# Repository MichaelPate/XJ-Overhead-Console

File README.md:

# XJ-Overhead-Console
Overhead Console Trip Computer for a 1990 Jeep Cherokee XJ. The goal is to display things like gyroscope readings and log GPS points.

The overhead console, or trip computer, should display the folling data by the time its fully complete:
- RTC time and date
- Temperature, pressure, humidity, both inside/outside
  - A remote mount sensor would be needed, with likely wireless radio communications
- Compass heading (cardinal and degrees)
- GPS latitude and longitude
- GPS speed (if accurate enough)
- GPS distance (calculated from sum of prior points or line-of-sight)
- Gyroscope roll and pitch
  - Gyroscope should be able to be zeroed
- Accelerometer readings that are above a threshold
  - Threshold should be settable
- System voltage
- The computer should know if the car is running or not
- The hardware circuit should provide a couple spare analog and digital IO for future use

The trip computer should be able to control the folling
- Off road lights (through relays)
  - User control of lights acheived through toggle switches
  - The ability to control off road lights gives the ability to alarm
- The horn (through a relay)
  - User control of horn acheived through pull cord mounted on side of head console
  - The ability to control the horn gives the ability to alarm
- A GSM module capable of sending SMS messages
  - This allows for GPS location in the event of a theft
  - Or possibly sending SOS messages to contacts in the event of an emergency
  - Or possibly remote kill switch capability

The trip computer should have the ability to connect to an SD card or USB flash drive:
- This allows for datalogging of all sensor data for later viewing
- Control of datalogging would be minimal. Auto generated file names.
  - User control of datalogging would be through a push button or toggle switch

A possible feature would be alarming. The alarm state could be acheived
through significant detection of motion, a GPS reading outside a geo-fence, or a combination
The addition of a PIR sensor inside the cab is possible, if experimentation shows it to not be too sensetive to activity outside the car.

# Overhead Console Project #

**1 Project Scope**

The scope of the project is to design a computer controller for a car that can provide security functionality, environmental data, locationing/positioning, and basic data logger functionality.

**1.1 Security Functionality**

The controller can provide security through the means of a fuel pump interlock system. Such a system involves interrupting power to the fuel pump when a security state is active, and returning signal to the fuel pump when the security state is inactive.

Additional security measures that may be implemented in the future are alarming (controlling lights and horn), the ability to send SMS text messages containing GPS location data, and PIR/glass-break sensors to be mounted inside the cabin. Security events may be recorded to the SD card.

**1.2 Environmental Data**

Environmental data that the computer is responsible for gathering, logging, and displaying includes temperature, atmospheric pressure, both inside and outside the cabin. A real time clock is also present that will track the time of all events and provide a readout. A low outside temperature should lead to an indication for the risk of ice on roadways.

**1.3 Locationing/Positioning Data**

The computer is also responsible for tracking location/position data. This includes GPS coordinates, gyroscope readings for pitch and roll, accelerometer readings, and compass heading. If the GPS is deemed accurate enough, GPS indicated speed and altitude should also be reported.

**1.4 Datalogging Functionality**

All normal operation data should be, optionally, recorded to an SD card by way of an SD card reader/writer. The controller will keep track of empty space on the SD card and auto-generate file names, but will not have the ability to browse or change existing files. The user will control data logging through a toggle switch.

**2 Project Requirements**

The project will have requirements for user interface, sensors, hardware, power supply, external communications (antennae, ports).

**2.1 User Interface**

The user interface will consist of a 20x4 character LCD, push buttons, toggle switches, LEDs, and a piezo buzzer. There should be 3 push buttons for menu navigation and special functions. There should be one toggle switch for security functionality and one toggle switch for controlling data-logging functions. There should be 3 LEDs for displaying the following conditions: GPS lock, SD card error, and general error. There will also be hardware reset and power switches available, though hidden from normal use.

**2.2 Sensors and Hardware, Controller**

The controller used for this project is the STM32F401RE. Discrete IO, I2C, SPI, and UART buses will be used to communicate with all modules and hardware. Time will be tracked by an RTC module that is built into the controller and powered via external coin cell battery

The I2C bus will connect the controller to the BMP280 barometric pressure sensor, the GY273 magnetometer, the GY521 accelerometer, the SHT31 humidity sensor, and the 20x4 character LCD (HD44780 with PCF8574 I2C expander). The SPI bus will be used to connect the controller to the SD card module for data logging. This is currently the only device that will utilize the SPI bus. Two UARTS will be used, one for a connection to a PC via serial terminal, and the other will be used to connect the controller to the NEO-6M GPS module. The discrete analog and digital IO will be used to interface with the LEDs, piezo, push buttons, toggle switches, and an analog system battery voltage input (through a resistive voltage divider).

All hardware should be installed on a printed circuit board (PCB) of 2 or 4 layers. All UI elements should connect to the main circuit board through JST connectors. Power should be supplied via screw terminals. If a remote sensor is installed, data and power connections should be made using screw terminals. The PCB should be smaller than approximately 4.5” by 4.5.”

**2.3 Power Supply**

The controller will require 12VDC from the car’s electrical system to operate, in addition to a 12VDC keyed power signal from the car’s ignition control. The 12VDC power will be used to power all functions through the use of buck converters, which will generate the 5VDC and 3.3VDC voltages required to operate the controller and its hardware. The total power load on the car’s electrical system should be less than 10W. The 12V keyed power input will be used for signal only by the controller. The circuit board should contain two fuses: one fuse for the controller itself and another for a 5V USB port made available for other devices.

**2.4 External Ports and Connections**

The controller enclosure will require ports for power supply, remote signaling, and GPS antenna mounting. Appropriate panel mount connectors should be used to allow for easy installation and uninstallation. A panel mount 5V USB port should be provided, connected to the main 12V power supply through a fuse. This port will be optionally used for powering a dashboard camera. If appropriate, a cutoff circuit should be implemented such that the USB port is disabled if the system voltage drops below a threshold.

The GPS antenna should be mounted such that it faces towards the windshield of the car and has as few line of sight (LOS) restrictions as possible to the outside of the car. If required, an external mounting antenna could be installed, ran to the controller enclosure in the same manner as a remote sensor.

As described above, a hardware power switch and a hardware reset button should be available to the user, though hidden. The enclosure should be designed with a hatch covering these devices. Such devices should be connected to the circuit board using appropriate connectors.

**2.5 Mounting Location and Enclosure**

The goal of this project is to design an overhead console trip computer for use in a car. Such an enclosure would be mounted to the roof of a car’s interior, towards the front. The enclosure should be either adapted into an existing overhead console or 3D printed in a box that can be mounted to the roof of a car. The LCD should be angled such that it is readable from the driver of the car. UI elements like buttons should be installed in front of the LCD but far enough away from it so as to not interfere with its visibility. See Figure 1.1 for an example design.

_Figure 1.1. Example enclosure design._

**3 Controller Theory of Operation**

The controller should operate in four main states: Idle, Security, Initialization, and Running. Settings for configuring the system parameters can be accessed through a connection to a PC using a serial terminal. The overall system state machine is depicted in Figure 1.2.

_Figure 1.2. Overall Controller State Machine._

**3.1 Idle State**

The idle state is the default state of the machine after a reset. After a power-on or reset, the system will be placed into the Idle state and the system will need the presence of 12V keyed power to proceed into the Initialization state.

Entry into the Idle state will cause the system to check the security toggle switch exactly once right at the entry into Idle and will go into Security if the toggle switch is activated. This is to prevent an attacker from disabling the security system by removing and replacing the battery terminal before attempting to start the car. This system can be defeated by removing all power to the system, toggling the security switch off, and replacing power to the vehicle. This is not considered a problem, because the security toggle will remain unlabeled on the enclosure, and only those with training are likely to recognize it as a security device.

In normal operation, the idle state is reached when the car is turned off and the security features are disabled. The controller will consider the loss of 12V keyed power as the signal to enter the Idle state. In Idle, all peripherals except the real time clock (RTC) are disabled, and the CPU should enter a low power mode to save battery charge. The CPU should look for the return of 12V keyed power as a signal to exit Idle and enter the Initialization state. The CPU can only return to the Initialization state from Idle upon the detection of 12V keyed power. Enabling or disabling the security features through the toggle switch will have no impact on the transition from Idle to Initialization once the CPU has reached a low power mode. In Idle state, the fuel pump interlock relay should always be deactivated, so that the fuel pump can be controlled by the car’s ignition systems as normal. The procedure for the Idle state is shown below in Figure 1.3.

_Figure 1.3. Idle state procedure._

**3.2 Security State**

When the security features are enabled by the toggle switch, only when the controller is in the Running state, the system will enter Security state instead of Idle state when 12V keyed power is lost. In this state, the CPU should disable all peripherals except any security devices and the RTC. In this state, any security alarm conditions will also be monitored, and the setting and resetting of any alarm behavior is controlled. The fuel pump interlock relay will be enabled so that power cannot be sent to the fuel pump by the car’s ignition signal. When 12V keyed power is returned to the system, the controller will wake from sleep transition to Initialization. In Security state, the security features toggle switch will have no effect, and will not transition the system from Security to Initialization. The Running state is the only state where this toggle switch will have effect. The procedure for the Security state is below in Figure 1.4.

_Figure 1.4. Security state procedure._

**3.3 Initialization State**

The initialization state is responsible for configuring all hardware and preparing for the Running state. This state will also process the hand-off between Security and Running states. In this state, the first action will be to initialize the UI elements, before configuring and initializing the sensors. This state will display a splash screen on the LCD while the sensors are configured. The procedure for the Initialization state is in Figure 1.5 on the next page.

If the previous state was the Security state, the user will be expected to enter a passcode in this state before the Running state can be entered. In this state, the fuel pump interlock will remain activated until the correct passcode is entered. To maintain security, there will be no specific prompt for the passcode on the display, and the user will need to enter this passcode using the menu buttons. The passcode will be a number consisting of 2 digits. There is no limit on attempts, the system will remain in this state until the correct passcode is entered. However, if an incorrect passcode is entered, a delay of 5 seconds will be imposed before the UI will respond to another passcode entry.

After displaying the splash screen and the user entering a valid passcode, but before configuring the sensors, the system will check for a UART connection to a PC. This will last a couple seconds, and the system will wait for the user to input data from a PC serial terminal. If a connection is detected, the system will prompt the user to change parameters. The following parameters are settable by the user in this mode: RTC time, security passcode, LCD display interval, data logging interval. The user can send a command to end the configuration, and the system will proceed. Unless this command is issued, the system will wait for further input from the UART. If a UART connection was established, the system will continue to output system status messages as needed until it enters either the Idle or Security states after a loss of 12V keyed power.

The Initialization state will automatically enter the Running state when the correct passcode is entered (if the prior state was Security), all sensors have been configured, and a UART connection to a PC is not detected or the user completed UART configuration. In the event a sensor cannot be successfully configured, a general error should be raised (the UI should set the general error LED), the sensor skipped, and the system will still go into Running state. There will be no further attempts to configure a sensor if the first initialization attempt fails. The user will have to power cycle the computer or press a reset button.

_Figure 1.5. Initialization state procedure._

**3.4 Running State / Main Program Loop**

The Running state is for normal operation, when the car is running. In this state, all features and peripherals are running and the CPU is not in any low power mode. This is the only state where the data-logging control and security control toggles will have any effect. The Running state encapsulates the main program loop, which is responsible for reading sensor data, processing data, updating the UI, data logging, and determining which state to enter upon the loss of 12V keyed power.

The main program loop will consist of several subroutines. Each subroutine will be ran sequentially as a part of the procedure in Figure 1.6. Generally, the main program loop can be broken into three major segments: data processing, data logging, and user interface.

The data processing subroutine will communicate with each of the sensors and modules from Section 2.2 to request raw readings. Once all the raw data is gathered, it will be processed into final, usable data. Raw environment data will be converted to convenient units (Fahrenheit for temperature, inHg for pressure, etc), raw accelerometer readings will be computed into gyroscope pitch and roll, and magnetometer readings will be converted into compass headings. GPS data will also be collected, though it will not need to be processed.

On an interval specified by the configuration parameters (or a default if not set), the data logging subroutine will save the data to a file on the SD card. All data logged will be time stamped with the time from the RTC and will be in the same single file. A program on a PC will be required to separate the data logs based on timestamp.

The user interface subroutine has two components. One component will run once per loop and handle menu buttons and LEDs (physical component). The other component will run every time the LCD timer meets a defined interval (display component). The display component of the user interface subroutine will be controlled by the menu buttons. The user can cycle through screens as defined in the next section. As a part of the display component, the system will output data through the UART, if a UART connection was established during the Initialization state.

At the end of all the subroutines in the program loop, the controller will check the status of the 12V keyed power input. If keyed power is lost, the system will first evaluate the data logging toggle. If data logging was enabled, the controller will stop the datalogging and de-initialize the SD card. Then, the controller will evaluate the security toggle. If activated, the controller will activate the fuel pump interlock before proceeding into the Security state. If the security toggle is deactivated, the controller will proceed into the Idle state.

_Figure 1.6. Running state procedure._

**4 User Interface**

The user interface consists of the physical component (push buttons and LEDs) and the display component (LCD and potentially VFD). These components are only utilized in the Initialization and Running states.

The three menu buttons available to the user are principally used for selecting the data screen to be displayed. The leftmost button corresponds to “left” or “up,” and the rightmost button corresponds to “right” or “down.” The center button corresponds to “OK” or “back,” depending on the context of the display.

The behavior of the buttons is different during the Initialization state, however. The leftmost button is used to select the first digit of the passcode, cycling between all numbers from 0 to 9. The center button is used in the same manner but for the second digit of the passcode. The rightmost button is to submit the entered number to be checked against the passcode stored in memory. As stated above, an incorrect passcode entry will result in a 5 second delay before the UI accepts another passcode. When asking for a passcode during the Initialization state, the display will only show the entered numbers, and will not show a prompt for the passcode. This is to avoid making the computer appear as a security device, which would gather attention from attackers.

The three LEDs on the enclosure will be enabled or disabled according to their function. One LED will represent a GPS signal lock, and will be turned on whenever valid results are being received from the GPS module. Another LED is for a SD card error, which would be detected by the data logging subroutine. This LED being lit means that data logging is not taking place, regardless of the data logging toggle switch. The third LED is for general errors. These errors would include, but not be limited to, sensor initialization errors found in the Initialization state. If the general error LED is lit, the controller will need to enter the Initialization state again, to re-initialize all modules. This can be done by reset, power cycling, or by turning the car off and then on.

As described earlier, the menu buttons can be used to cycle between various data displays. There are 5 available data screens to choose from: Summary, Environment, GPS, Gyroscope, and Trip Log. The menu buttons will cycle through this list of screens in a loop.

The Summary data screen will show a mix of information from the other categories. At a minimum it will display the time and date, indoor and outdoor temperature, and compass heading. In cold weather, an ice warning will also be present. GPS speed may also be included. If a VFD is present, the VFD will always display the compass heading and outdoor temperature.

The Environment data screen will show all data from environment sensors, including: pressure, indoor/outdoor temperature, humidity, and altitude. An ice warning will also be present in cold weather.

The GPS data screen will show the GPS coordinates of the vehicle, in latitude and longitude. GPS calculated speed, heading, and altitude may also be shown. Magnetometer computed compass heading will be shown as well.

The Gyroscope data screen will show the accelerometer readings computed as pitch and roll. In this screen, the center button can be used to zero the gyroscope, for taking relative readings. A compass heading will also be displayed here. Pre-defined alarms for pitch and roll will be displayed on screen, should the gyroscope produce values above the defined thresholds.

The Trip Log screen will show data pertaining to the SD card. This includes the size of the file on the card, or space remaining. It will also show the amount of time since the log was first started, or when the vehicle was last started, whichever happened last. If data logging is not enabled (the toggle is deactivated or an SD card error is present), this data screen will show an error.

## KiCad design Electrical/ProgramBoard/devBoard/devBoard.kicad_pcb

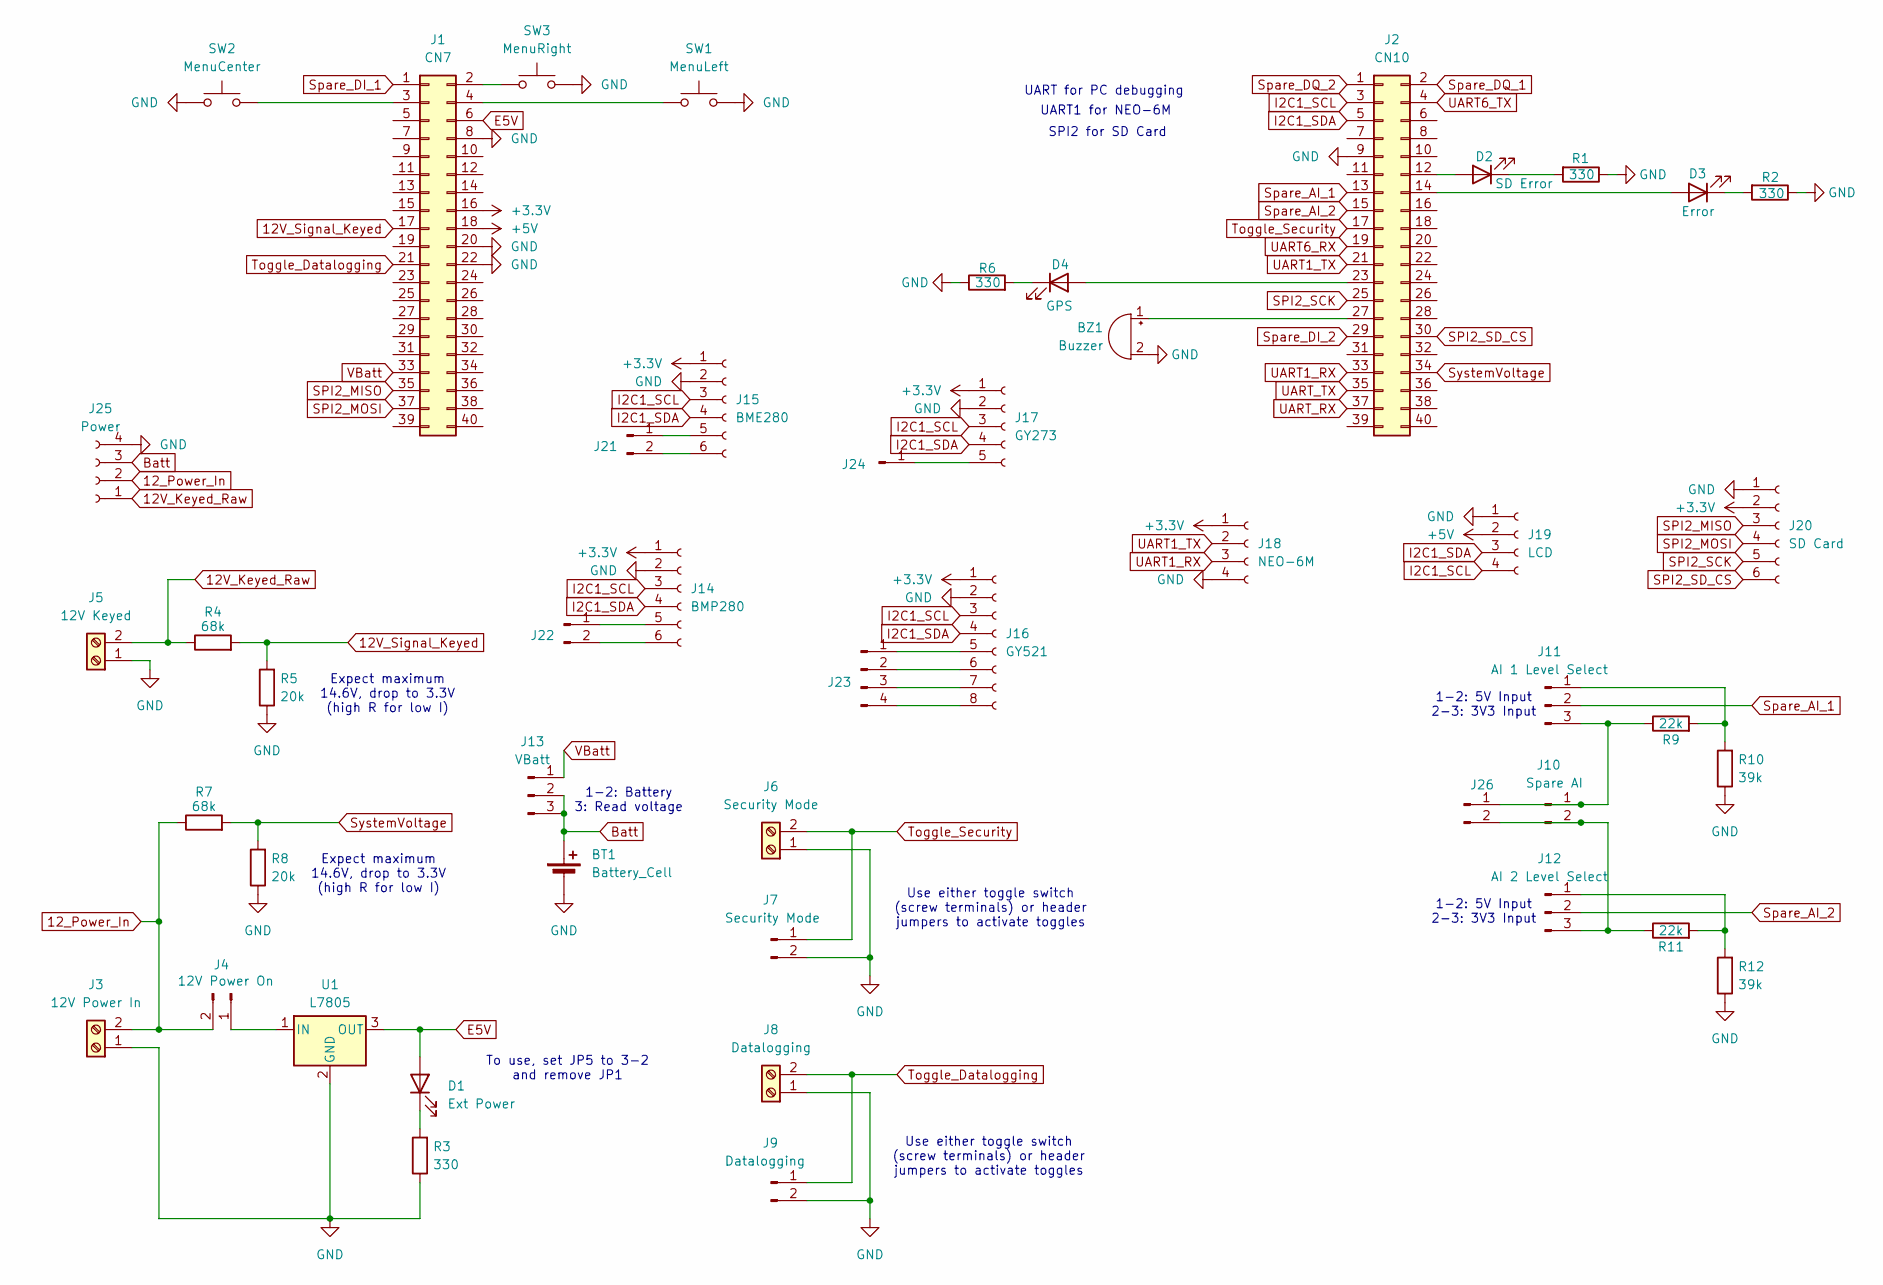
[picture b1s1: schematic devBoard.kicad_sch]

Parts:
BT1: Battery_Cell; Battery_Panasonic_CR2032-HFN_Horizontal_CircularHoles
BZ1: Buzzer; Buzzer_12x9.5RM7.6
D1: Ext Power; LED_D5.0mm
D2: SD Error; LED_D5.0mm
D3: Error; LED_D5.0mm
D4: GPS; LED_D5.0mm
J1: CN7; PinSocket_2x20_P2.54mm_Vertical
J2: CN10; PinSocket_2x20_P2.54mm_Vertical
J3: 12V Power In; TerminalBlock_RND_205-00012_1x02_P5.00mm_Horizontal
J4: 12V Power On; PinHeader_1x02_P2.54mm_Vertical
J5: 12V Keyed; TerminalBlock_RND_205-00012_1x02_P5.00mm_Horizontal
J6: Security Mode; TerminalBlock_RND_205-00012_1x02_P5.00mm_Horizontal
J7: Security Mode; PinHeader_1x02_P2.54mm_Vertical
J8: Datalogging; TerminalBlock_RND_205-00012_1x02_P5.00mm_Horizontal
J9: Datalogging; PinHeader_1x02_P2.54mm_Vertical
J10: Spare AI; PinHeader_1x02_P2.54mm_Vertical
J11: AI 1 Level Select; PinHeader_1x03_P2.54mm_Vertical
J12: AI 2 Level Select; PinHeader_1x03_P2.54mm_Vertical
J13: VBatt; PinHeader_1x03_P2.54mm_Vertical
J14: BMP280; PinSocket_1x06_P2.54mm_Vertical
J15: BME280; PinSocket_1x06_P2.54mm_Vertical
J16: GY521; PinSocket_1x08_P2.54mm_Vertical
J17: GY273; PinSocket_1x05_P2.54mm_Vertical
J18: NEO-6M; PinSocket_1x04_P2.54mm_Vertical
J19: LCD; PinSocket_1x04_P2.54mm_Vertical
J20: SD Card; PinSocket_1x06_P2.54mm_Vertical
J21, J22: PinHeader_1x02_P2.54mm_Vertical
J23: PinHeader_1x04_P2.54mm_Vertical
J24: PinHeader_1x01_P2.54mm_Vertical
J25: Power; PinSocket_1x04_P2.54mm_Vertical
J26: Spare AI; PinSocket_1x02_P2.54mm_Vertical
R1, R2, R3, R6: 330; R_Axial_DIN0207_L6.3mm_D2.5mm_P10.16mm_Horizontal
R4, R7: 68k; R_Axial_DIN0207_L6.3mm_D2.5mm_P10.16mm_Horizontal
R5, R8: 20k; R_Axial_DIN0207_L6.3mm_D2.5mm_P10.16mm_Horizontal
R9, R11: 22k; R_Axial_DIN0207_L6.3mm_D2.5mm_P10.16mm_Horizontal
R10, R12: 39k; R_Axial_DIN0207_L6.3mm_D2.5mm_P10.16mm_Horizontal
SW1: MenuLeft; SW_PUSH_6mm
SW2: MenuCenter; SW_PUSH_6mm
SW3: MenuRight; SW_PUSH_6mm
U1: L7805; TO-220-3_Vertical

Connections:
12V_Keyed_Raw: J5.2, J25.1, R4.1
12V_Signal_Keyed: J1.17, R4.2, R5.2
12_Power_In: J3.2, J4.2, J25.2, R7.1
+3.3V: J1.16, J14.1, J15.1, J16.1, J17.1, J18.1, J20.2
+5V: J1.18, J19.2
Batt: BT1.1 (+), J13.2, J13.3, J25.3
E5V: D1.2 (A), J1.6, U1.3 (OUT)
GND: BT1.2 (-), BZ1.2 (-), J1.8, J1.20, J1.22, J2.9, J3.1, J5.1, J6.1, J7.2, J8.1, J9.2, J14.2, J15.2, J16.2, J17.2, J18.4, J19.1, J20.1, J25.4, R1.1, R2.1, R3.1, R5.1, R6.1, R8.1, R10.1, R12.1, SW1.2, SW2.1, SW3.2, U1.2 (GND)
I2C1_SCL: J2.3, J14.3, J15.3, J16.3, J17.3, J19.4
I2C1_SDA: J2.5, J14.4, J15.4, J16.4, J17.4, J19.3
unnamed: BZ1.1 (+), J2.27
unnamed: D1.1 (K), R3.2
unnamed: D2.2 (A), J2.12
unnamed: D2.1 (K), R1.2
unnamed: D3.2 (A), J2.14
unnamed: D3.1 (K), R2.2
unnamed: D4.2 (A), J2.23
unnamed: D4.1 (K), R6.2
unnamed: J1.2, SW3.1
unnamed: J1.3, SW2.2
unnamed: J1.4, SW1.1
unnamed: J4.1, U1.1 (IN)
unnamed: J10.1, J11.3, J26.1, R9.1
unnamed: J10.2, J12.3, J26.2, R11.1
unnamed: J11.1, R9.2, R10.2
unnamed: J12.1, R11.2, R12.2
unnamed: J14.5, J22.1
unnamed: J14.6, J22.2
unnamed: J15.5, J21.1
unnamed: J15.6, J21.2
unnamed: J16.5, J23.1
unnamed: J16.6, J23.2
unnamed: J16.7, J23.3
unnamed: J16.8, J23.4
unnamed: J17.5, J24.1
SPI2_MISO: J1.35, J20.3
SPI2_MOSI: J1.37, J20.4
SPI2_SCK: J2.25, J20.5
SPI2_SD_CS: J2.30, J20.6
Spare_AI_1: J2.13, J11.2
Spare_AI_2: J2.15, J12.2
Spare_DI_1: J1.1
Spare_DI_2: J2.29
Spare_DQ_1: J2.2
Spare_DQ_2: J2.1
SystemVoltage: J2.34, R7.2, R8.2
Toggle_Datalogging: J1.21, J8.2, J9.1
Toggle_Security: J2.17, J6.2, J7.1
UART1_RX: J2.33, J18.3
UART1_TX: J2.21, J18.2
UART6_RX: J2.19
UART6_TX: J2.4
UART_RX: J2.37
UART_TX: J2.35
VBatt: J1.33, J13.1

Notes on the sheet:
Expect maximum 14.6V, drop to 3.3V (high R for low I)
UART1 for NEO-6M
Use either toggle switch (screw terminals) or header jumpers to activate toggles
UART for PC debugging
1-2: 5V Input 2-3: 3V3 Input
1-2: Battery 3: Read voltage
SPI2 for SD Card
To use, set JP5 to 3-2 and remove JP1

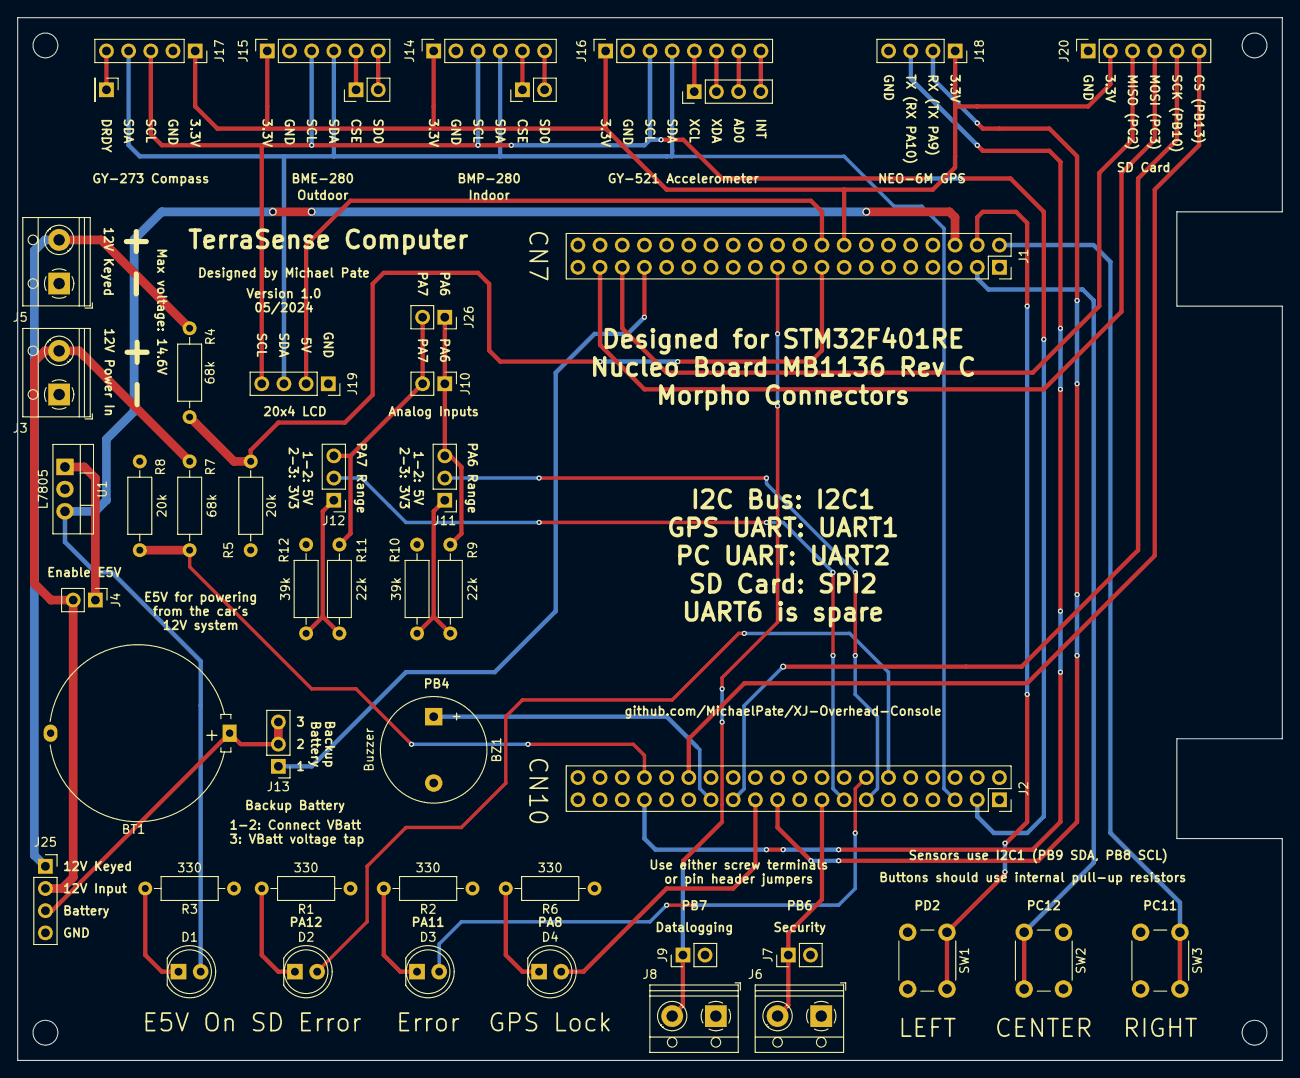
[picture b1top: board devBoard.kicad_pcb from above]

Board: 2 copper layers, 144.8 x 119.4 mm, 48 parts (0 on the bottom side), 47 nets.

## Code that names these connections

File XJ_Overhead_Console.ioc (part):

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Mcu.Name=STM32F401R(D-E)Tx
Mcu.Package=LQFP64
Mcu.UserName=STM32F401RETx
PA10.Mode=Asynchronous
PA10.Signal=USART1_RX
PA11.GPIOParameters=GPIO_Label
PA11.GPIO_Label=General_Error_LED
PA11.Signal=GPIO_Output
PA12.GPIOParameters=GPIO_Label
PA12.GPIO_Label=SD_Card_Error_LED
PA12.Signal=GPIO_Output
PA13.GPIOParameters=GPIO_Label
PA13.GPIO_Label=TMS
PA13.Mode=Serial_Wire
PA13.Signal=SYS_JTMS-SWDIO
PA14.GPIOParameters=GPIO_Label
PA14.GPIO_Label=TCK
PA14.Mode=Serial_Wire
PA14.Signal=SYS_JTCK-SWCLK
PA15.GPIOParameters=GPIO_PuPd,GPIO_Label
PA15.GPIO_Label=Signal_12VKeyed
PA15.GPIO_PuPd=GPIO_PULLUP
PA15.Signal=GPIO_Input
PA2.GPIOParameters=GPIO_Speed,GPIO_PuPd,GPIO_Label,GPIO_Mode
PA2.GPIO_Label=USART_TX
PA2.GPIO_Mode=GPIO_MODE_AF_PP
PA2.GPIO_PuPd=GPIO_NOPULL
PA2.GPIO_Speed=GPIO_SPEED_FREQ_LOW
PA2.Mode=Asynchronous
PA2.Signal=USART2_TX
PA3.GPIOParameters=GPIO_Speed,GPIO_PuPd,GPIO_Label,GPIO_Mode
PA3.GPIO_Label=USART_RX
PA3.GPIO_Mode=GPIO_MODE_AF_PP
PA3.GPIO_PuPd=GPIO_NOPULL
PA3.GPIO_Speed=GPIO_SPEED_FREQ_LOW
PA3.Mode=Asynchronous
PA3.Signal=USART2_RX
PA5.GPIOParameters=GPIO_Speed,GPIO_PuPd,GPIO_Label,GPIO_Mode
PA5.GPIO_Label=LD2 [Green Led]
PA5.GPIO_Mode=GPIO_MODE_OUTPUT_PP
PA5.GPIO_PuPd=GPIO_NOPULL
PA5.GPIO_Speed=GPIO_SPEED_FREQ_LOW
PA5.Signal=GPIO_Output
PA6.GPIOParameters=GPIO_Label
PA6.GPIO_Label=Spare_AI_1
PA6.Signal=ADCx_IN6
PA7.GPIOParameters=GPIO_Label
PA7.GPIO_Label=Spare_AI_2
PA7.Signal=ADCx_IN7
PA8.GPIOParameters=GPIO_Label
PA8.GPIO_Label=GPS_Lock_LED
PA8.Signal=GPIO_Output
PA9.Mode=Asynchronous
PA9.Signal=USART1_TX
PB10.Mode=Full_Duplex_Master
PB10.Signal=SPI2_SCK
PB13.GPIOParameters=GPIO_Label
PB13.GPIO_Label=SDCard_CS
PB13.Signal=GPIO_Output
PB3.GPIOParameters=GPIO_Label
PB3.GPIO_Label=SWO
PB3.Signal=SYS_JTDO-SWO
PB4.GPIOParameters=GPIO_Speed,GPIO_Label
PB4.GPIO_Label=Piezo
PB4.GPIO_Speed=GPIO_SPEED_FREQ_HIGH
PB4.Signal=GPIO_Output
PB5.GPIOParameters=GPIO_Label
PB5.GPIO_Label=Spare_DI_2
PB5.Signal=GPIO_Input
PB6.GPIOParameters=GPIO_Label
PB6.GPIO_Label=Toggle_Security
PB6.Signal=GPIO_Input
PB7.GPIOParameters=GPIO_Label
PB7.GPIO_Label=Toggle_Datalogging
PB7.Signal=GPIO_Input
PB8.GPIOParameters=GPIO_Pu
PB8.GPIO_Pu=GPIO_PULLUP
PB8.Mode=I2C
PB8.Signal=I2C1_SCL
PB9.GPIOParameters=GPIO_Pu
PB9.GPIO_Pu=GPIO_PULLUP
PB9.Mode=I2C
PB9.Signal=I2C1_SDA
PC10.GPIOParameters=GPIO_Label
PC10.GPIO_Label=Spare_DI_1
PC10.Signal=GPIO_Input
PC11.GPIOParameters=GPIO_PuPd,GPIO_Label
PC11.GPIO_Label=MenuButtonRight
PC11.GPIO_PuPd=GPIO_PULLUP
PC11.Signal=GPIO_Input
PC12.GPIOParameters=GPIO_PuPd,GPIO_Label
PC12.GPIO_Label=MenuButtonCenter
PC12.GPIO_PuPd=GPIO_PULLUP
PC12.Signal=GPIO_Input
PC13-ANTI_TAMP.GPIOParameters=GPIO_PuPd,GPIO_Label,GPIO_ModeDefaultEXTI
PC13-ANTI_TAMP.GPIO_Label=B1 [Blue PushButton]
PC13-ANTI_TAMP.GPIO_ModeDefaultEXTI=GPIO_MODE_IT_FALLING
PC13-ANTI_TAMP.GPIO_PuPd=GPIO_NOPULL
PC13-ANTI_TAMP.Signal=GPXTI13
PC14-OSC32_IN.Mode=LSE-External-Oscillator
PC14-OSC32_IN.Signal=RCC_OSC32_IN
PC15-OSC32_OUT.Mode=LSE-External-Oscillator
PC15-OSC32_OUT.Signal=RCC_OSC32_OUT
PC2.Mode=Full_Duplex_Master
PC2.Signal=SPI2_MISO
PC3.Mode=Full_Duplex_Master
PC3.Signal=SPI2_MOSI
PC4.GPIOParameters=GPIO_Label
PC4.GPIO_Label=SystemVoltage
PC4.Signal=ADCx_IN14
PC6.Mode=Asynchronous
PC6.Signal=USART6_TX
PC7.Mode=Asynchronous
PC7.Signal=USART6_RX
PC8.GPIOParameters=GPIO_Label
PC8.GPIO_Label=Spare_DQ_1
PC8.Signal=GPIO_Output
PC9.GPIOParameters=GPIO_Label
PC9.GPIO_Label=Spare_DQ_2
PC9.Signal=GPIO_Output
PD2.GPIOParameters=GPIO_PuPd,GPIO_Label
PD2.GPIO_Label=MenuButtonLeft
PD2.GPIO_PuPd=GPIO_PULLUP
PD2.Signal=GPIO_Input
PH0\ -\ OSC_IN.Mode=HSE-External-Clock-Source
PH0\ -\ OSC_IN.Signal=RCC_OSC_IN
PH1\ -\ OSC_OUT.Mode=HSE-External-Clock-Source
PH1\ -\ OSC_OUT.Signal=RCC_OSC_OUT
RCC.HSE_VALUE=8000000
RCC.SYSCLKFreq_VALUE=84000000
RCC.SYSCLKSource=RCC_SYSCLKSOURCE_PLLCLK
board=NUCLEO-F401RE
boardIOC=true

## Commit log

2024-05-03 Add empty project
2024-05-03 Autogenerated Project Files
2024-05-03 Add empty KiCAD project
2024-05-03 Add kicad project changes
2024-05-03 Add empty project archive
2024-05-03 RTC test code
2024-05-03 Add documentation
2024-05-03 update serial printing
2024-05-03 refactor to align with standards
2024-05-04 RTC tested working. UART output tested working.
2024-05-04 Updated .elf file
2024-05-04 Add source for printf() fix
2024-05-04 regenerate files for UART ISR
2024-05-04 add test UART RX code
2024-05-04 add .elf file
2024-05-04 fixing file changes
2024-05-04 UART DMA RX working
2024-05-04 uart rx still blocking but dma ch open
2024-05-04 interrupts not working, back to blocking
2024-05-04 no need for DMA tx, aborting
2024-05-04 DMA RX is working!
2024-05-04 added notes so I dont forget
2024-05-04 updating .elf file
2024-05-04 Add ability to set RTC over UART2
2024-05-05 cleanup code
2024-05-05 more refactoring
2024-05-05 i2c scanner implemented
2024-05-05 add lcd library files
2024-05-05 add lcd header file
2024-05-05 LCD library complete, needs tested
2024-05-05 LCD I2C Library tested working
2024-05-06 Adjust RTC synch predivider since RTC runs fast
2024-05-06 Remove LCD calls and add bmp library files
2024-05-06 BMP280 library complete, needs tested
2024-05-07 Basic comms acheived for BMP280
2024-05-07 BMP raw vals work, conversion doesnt
2024-05-08 Add more docs
2024-05-08 Add image files
2024-05-10 Implement overarching state machine
2024-05-13 Create development PCB, send for fab
